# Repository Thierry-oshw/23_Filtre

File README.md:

# 23_Filtre_PB
 Filtre Passe Bande

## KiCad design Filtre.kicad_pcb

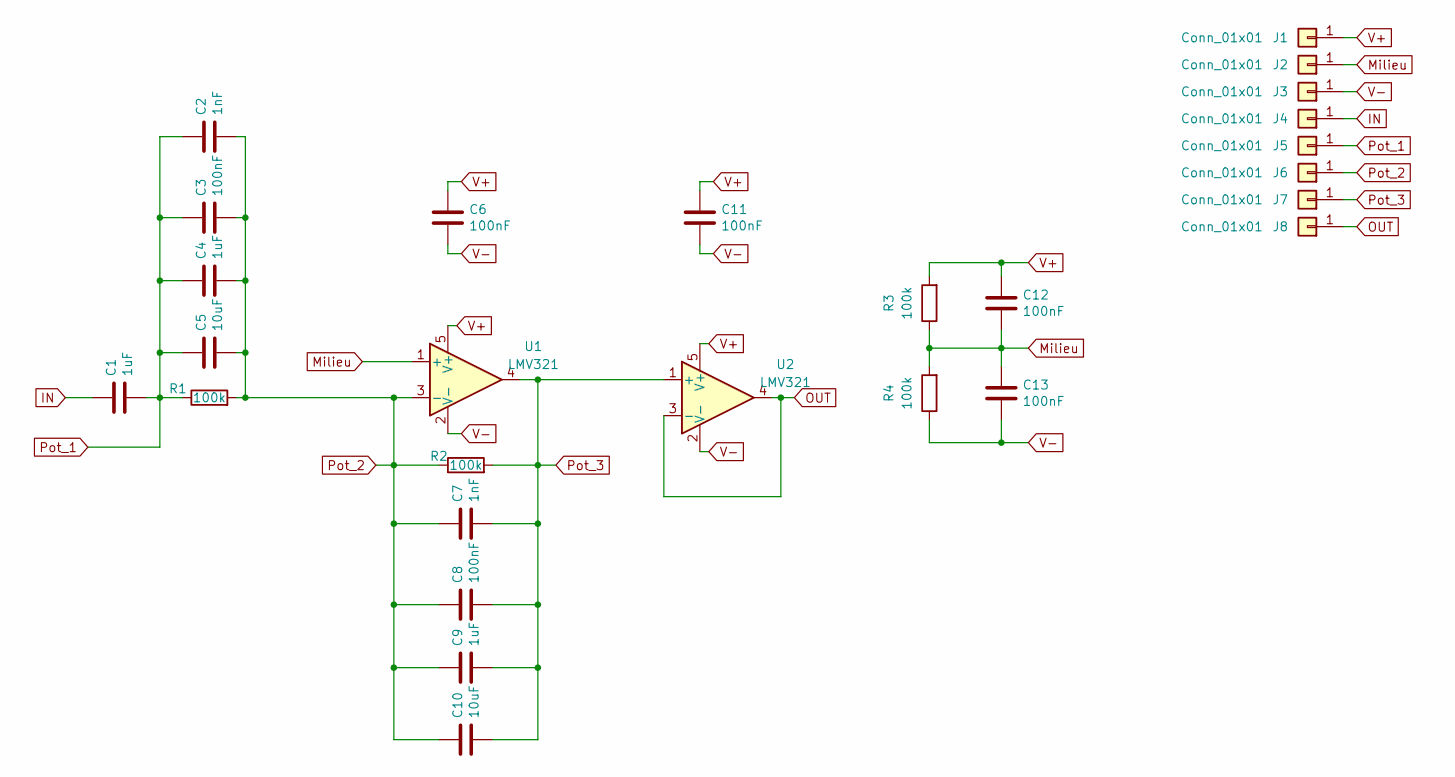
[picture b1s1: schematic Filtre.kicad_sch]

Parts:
C1, C4, C9: 1uF; C_0603_1608Metric; LCSC C15849
C2, C7: 1nF; C_0603_1608Metric; LCSC C1588
C3, C6, C8, C11, C12, C13: 100nF; C_0603_1608Metric; LCSC C14663
C5, C10: 10uF; C_0603_1608Metric; LCSC C96446
J1, J2, J3, J4, J5, J6, J7, J8: Conn_01x01; Castellated_conn
R1, R2, R3, R4: 100k; R_0603_1608Metric; LCSC C25803
U1, U2: LMV321; SOT-23-5; LCSC C7972

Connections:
IN: C1.2, J4.1
Milieu: C12.1, C13.2, J2.1, R3.1, R4.2, U1.1 (+)
OUT: J8.1, U2.3 (-), U2.4
Pot_1: C1.1, C2.2, C3.2, C4.2, C5.2, J5.1, R1.1
Pot_2: C2.1, C3.1, C4.1, C5.1, C7.2, C8.2, C9.2, C10.2, J6.1, R1.2, R2.1, U1.3 (-)
Pot_3: C7.1, C8.1, C9.1, C10.1, J7.1, R2.2, U1.4, U2.1 (+)
V+: C6.2, C11.2, C12.2, J1.1, R3.2, U1.5 (V+), U2.5 (V+)
V-: C6.1, C11.1, C13.1, J3.1, R4.1, U1.2 (V-), U2.2 (V-)

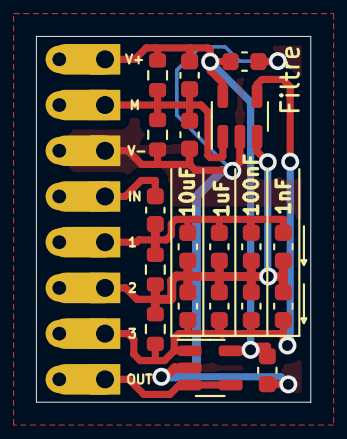
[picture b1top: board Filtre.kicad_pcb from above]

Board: 2 copper layers, 15.2 x 20.3 mm, 27 parts (0 on the bottom side), 8 nets.

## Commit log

2023-06-03 schema + placement + routage
